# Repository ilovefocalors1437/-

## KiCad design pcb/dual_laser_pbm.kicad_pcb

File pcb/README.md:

# Dual-laser PBM head, REV 0.1 MOCK

This is a **mock reconstruction**. It stands in for the original design file, which is on another laptop. The schematic is not known, so this is a plausible, electrically sensible board built from scratch. It is not a copy of the original and may differ from it in every detail. The silkscreen says `REV 0.1 MOCK` on both sides.

It is a 2-layer KiCad 7 board for a photobiomodulation head with two laser diodes aimed at the foot fascia:

- **LD1, 660 nm (red):** the shallower channel. Design intent: help local blood flow.
- **LD2, 850 nm (near-IR):** the deeper channel, aimed at the fascia itself. Design intent: help loosen the hyaluronan (HA) layer in densified fascia.

Both are the user's design intent, not established clinical effects.

## Files

| Path | What |
|---|---|
| `dual_laser_pbm.kicad_pcb`, `.kicad_pro` | The board (KiCad 7.0). There is no schematic file; nets are assigned in the script. |
| `generate_board.py` | Builds the board with the pcbnew API: placement table, a small grid A* router with rip-up/retry, GND pours, stitching vias, silkscreen, DRC. |
| `drc_report.txt` | KiCad DRC output for the generated board. |
| `fab/` | Gerbers (F/B Cu, mask, silk, paste, Edge.Cuts), Excellon drill + drill map, pick-and-place CSV. |
| `renders/board-top.png`, `board-bottom.png` (+ `.svg`) | 2D renders from the real geometry (bottom is mirrored, as seen from below). |
| `renders/kicad-top.*`, `kicad-bottom.svg` | Raw `kicad-cli` SVG plots for reference. kicad-cli 7 draws bottom silk under the pour, so use `board-bottom.png` or the Gerber for bottom silk. |
| `export_viewer_data.py` → `viewer/board.json` | Board geometry for the 3D viewer: outline, drills, tracks, vias, pads, filled zones, silk, footprints. |
| `viewer/dual-laser-3d.html` | Interactive three.js viewer. Loads `board.json` from the same folder. |
| `renders/viewer-*.png` | Viewer screenshots (desktop and phone, light and dark, lasers on, bottom, net highlight, exploded). |

## Regenerate

Needs Ubuntu 24.04 with `kicad` 7.0.x, `kicad-footprints` and `librsvg2-bin`, and the system Python (`/usr/bin/python3`, which has `pcbnew`).

```sh
./build.sh     # board + DRC, fab outputs, viewer/board.json, 2D renders
```

The router is deterministic (the script pins `PYTHONHASHSEED`), so a rebuild gives the same geometry. Item UUIDs in the `.kicad_pcb` differ between runs. For the DRC footprint-vs-library check, KiCad needs a global `fp-lib-table` (copy `/usr/share/kicad/template/fp-lib-table` to `~/.config/kicad/7.0/`).

## Blocks

- **Power in:** J1 USB-C 6-pin power-only receptacle, R1/R2 5.1 k CC pull-downs, F1 500 mA PTC, D1 SMF5.0A TVS, C1 22 µF → +5V. U1 AP2112K-3.3 LDO (C2/C3) → +3V3 for the MCU.
- **MCU:** U2 STM32G030F6P6 (TSSOP-20), C4/C5 decoupling, C6 on NRST. J3 1×5 2.54 mm SWD header (3V3, SWCLK, GND, SWDIO, NRST). SW1 button on PA0. Status LEDs: D2 power (on +3V3), D3 660 active (PA2), D4 850 active (PA3).
- **Laser rail switch and interlock:** Q1 AO3401A P-FET switches +5V → VLD. R6 holds it off. Q2 2N7002 pulls Q1's gate down, but Q2's source only reaches GND through the J2 interlock loop, so VLD needs **MCU LASER_EN (PA12) AND a closed loop**. R7 keeps LASER_EN low during reset. The MCU reads the loop on PA11 (internal pull-up). D5 amber LED + R9 hang off VLD itself, so it is lit whenever the laser supply is live, whatever the firmware does. C7 10 µF on VLD.
- **Two constant-current channels** (ch1 = LD1, ch2 = LD2), one half of U3 MCP6002 each:
  MCU PWM (PA7 / PA6, TIM3) → 10 k / 1 k divider + 1 µF filter (R14/R15/C12, R19/R20/C14) → 0–0.30 V setpoint at IN+ → op-amp → 100 Ω gate resistor (R12/R17) → AO3400A sink (Q3/Q4) → 2.2 Ω 1206 sense (R11/R16) fed back to IN− through 1 k (R13/R18), 1 nF compensation from OUT to IN− (C11/C13). Full scale 0.30 V / 2.2 Ω = 136 mA. TP3/TP4 expose the sense voltages.
- **Laser protection:** each diode has a reverse Schottky (D6/D7, BAT60A) and 100 nF (C9/C10) across it.
- **Temperature:** TH1 10 k NTC (0603) between the cans, R10 10 k to +3V3, read on PA5 (ADC).
- **Lasers:** LD1/LD2 TO-56 (5.6 mm) 3-pin cans, KiCad `OptoDevice:LaserDiode_TO56-3`, 14 mm apart on the right edge, with a via-free ring around each can for a lens holder and a ring of GND thermal vias outside it.

## Design choices that differ from the brief

- Board is **58 × 38 mm** (brief: ~56 × 36) to give the router room. 4 × M2.5 plated holes on GND, 3 fiducials, 4 test points.
- The lasers are **14 mm apart** (brief: ~12) so two lens holders and the NTC fit between them.
- **No hardware interlock pull-up resistor.** The MCU's internal pull-up on PA11 does that job. This leaves a gap at R8 in the reference numbering.
- **Monitor photodiode unused:** pin 3 of each TO-56 (PD anode, assumed common-anode pinout) is tied to pin 2, which shorts the PD. Pinouts vary between laser diode vendors. Check the real part.
- Design rules: netclass clearance 0.15 mm, tracks 0.25 mm signal / 0.3 mm +3V3 / 0.6 mm for VBUS, +5V, VLD, LD cathodes and sense nodes, vias 0.6/0.3 mm, copper-to-edge 0.3 mm. The router aims for 0.2 mm, and the board also passes DRC with the clearance raised to 0.2 mm.
- MCU pins: PA0 BTN, PA2 LED_660, PA3 LED_850, PA5 NTC, PA6 PWM_850, PA7 PWM_660, PA11 interlock sense, PA12 LASER_EN, PA13/PA14 SWD. Unused pins (1, 2, 3, 8, 11, 15, 20) have no net, nor does U1 pin 4 (NC).

## Bill of materials

| Ref | Value | Footprint (KiCad 7 library) | Purpose |
|---|---|---|---|
| J1 | USB-C 6P power only | USB_C_Receptacle_GCT_USB4125-xx-x_6P_TopMnt_Horizontal | 5 V input |
| R1, R2 | 5.1k | R_0603_1608Metric | CC pull-downs (USB-C sink) |
| F1 | PTC 500 mA | Fuse_1206_3216Metric | Resettable input fuse |
| D1 | SMF5.0A | D_SOD-123F | TVS on +5V |
| C1 | 22 µF 10 V | C_1206_3216Metric | +5V bulk |
| U1 | AP2112K-3.3 | SOT-23-5 | 3.3 V LDO |
| C2, C3 | 1 µF | C_0603_1608Metric | LDO in/out |
| U2 | STM32G030F6P6 | TSSOP-20_4.4x6.5mm_P0.65mm | MCU |
| C4 / C5 / C6 | 100 nF / 1 µF / 100 nF | C_0603_1608Metric | MCU decoupling, NRST filter |
| J3 | SWD 1×5 | PinHeader_1x05_P2.54mm_Vertical | Programming header |
| SW1 | TL3342 | SW_SPST_TL3342 | Start/stop button |
| D2 / D3 / D4 | green / red / orange | LED_0603_1608Metric | Power / 660 active / 850 active |
| R3, R4, R5 | 1k | R_0603_1608Metric | Status LED resistors |
| Q1 | AO3401A | SOT-23 | High-side laser rail switch |
| R6 | 100k | R_0603_1608Metric | Q1 gate pull-up (off by default) |
| Q2 | 2N7002 | SOT-23 | Enable, sourced through the interlock |
| R7 | 100k | R_0603_1608Metric | LASER_EN pull-down |
| J2 | JST PH 2-pin | JST_PH_B2B-PH-K_1x02_P2.00mm_Vertical | Interlock loop |
| D5 | amber | LED_0603_1608Metric | Emission indicator on VLD |
| R9 | 1k | R_0603_1608Metric | Emission LED resistor |
| C7 | 10 µF | C_0805_2012Metric | VLD reservoir |
| U3 | MCP6002 | SOIC-8_3.9x4.9mm_P1.27mm | Dual op-amp, one loop per channel |
| C8 | 100 nF | C_0603_1608Metric | Op-amp decoupling |
| LD1 | 660 nm laser diode | LaserDiode_TO56-3 | Red channel |
| LD2 | 850 nm laser diode | LaserDiode_TO56-3 | Near-IR channel |
| Q3, Q4 | AO3400A | SOT-23 | Current sinks |
| R11, R16 | 2.2 Ω 1 % | R_1206_3216Metric | Current sense |
| R12, R17 | 100 Ω | R_0603_1608Metric | Gate resistors |
| R13, R18 | 1k | R_0603_1608Metric | Feedback resistors |
| C11, C13 | 1 nF | C_0603_1608Metric | Loop compensation |
| R14, R19 | 10k | R_0603_1608Metric | PWM divider top |
| R15, R20 | 1k | R_0603_1608Metric | PWM divider bottom |
| C12, C14 | 1 µF | C_0603_1608Metric | PWM filter |
| D6, D7 | BAT60A | D_SOD-323 | Reverse Schottky across each diode |
| C9, C10 | 100 nF | C_0603_1608Metric | Cap across each diode |
| TH1 | NTC 10k | R_0603_1608Metric | Temperature between the cans |
| R10 | 10k | R_0603_1608Metric | NTC divider |
| TP1–TP4 | +5V, +3V3, ISENSE1, ISENSE2 | TestPoint_Pad_D1.0mm | Test points |
| FID1–FID3 | | Fiducial_1mm_Mask2mm | Assembly fiducials |
| H1–H4 | M2.5 | MountingHole_2.7mm_M2.5_Pad | Mounting holes (GND) |

55 placed parts plus 4 test points, 3 fiducials and 4 holes (66 footprints).

## Nets (35)

Power: `VBUS` (J1 → F1), `+5V` (11 pads), `+3V3` (9), `VLD` (switched laser rail, 11), `GND` (36 pads; both layers poured and stitched).
Per laser channel n = 1, 2: `PWM_660`/`PWM_850`, `SETn`, `FBn`, `OUTn`, `GATEn`, `ISENSEn`, `LDn_K`.
Control: `LASER_EN`, `VLD_G`, `INTLK_LO`, `NTC_ADC`, `BTN`, `NRST`, `SWDIO`, `SWCLK`, `CC1`, `CC2`, `LED_660`, `LED_850`, `LEDA_PWR`, `LEDA_660`, `LEDA_850`, `LEDA_EMIT`.

Board stats: 539 track segments, 112 vias (routing + GND fanout + stitching), GND zones on F.Cu and B.Cu.

## What was verified, and what was not

Verified:
- KiCad 7 DRC (`pcbnew.WriteDRCReport`, all checks, zones filled): **0 violations, 0 unconnected pads, 0 footprint errors.** Also 0 clearance violations with the netclass clearance raised to 0.2 mm.
- Every net is routed. The connectivity check reports 0 unconnected items.
- Renders checked by eye: parts sit on their pads, there are no overlapping courtyards, and no silk sits on pads.

Not verified:
- No schematic, ERC, SPICE simulation or prototype. Values are textbook choices, not tuned.
- Q3/Q4 dissipate about 0.35 W each at full current from 5 V. That should be within an AO3400A's rating with this copper, but it was not thermally analysed.
- Footprint pinouts are taken from the KiCad libraries. The TO-56 pin assignment (which pin is common, whether the PD is common-anode) depends on the real laser part.
- Routing is machine-made. It is DRC-clean, but some signal runs are longer or more diagonal than a human would draw them, and +5V crosses under U2.
- Firmware does not exist. The PWM, interlock and NTC behaviour described here is what the hardware allows.

## Laser safety

A ~100 mW-class laser diode is Class 3B: direct or mirror-reflected beams can injure the eye. 850 nm is invisible, so there is no blink reflex and no visible cue that it is on. That is why this board has a hardware interlock, a hardware emission LED and current limits. A real device also needs wavelength-rated eyewear for anyone nearby, and a regulatory review (IEC 60825-1, plus medical-device rules if it is used on people) before use.

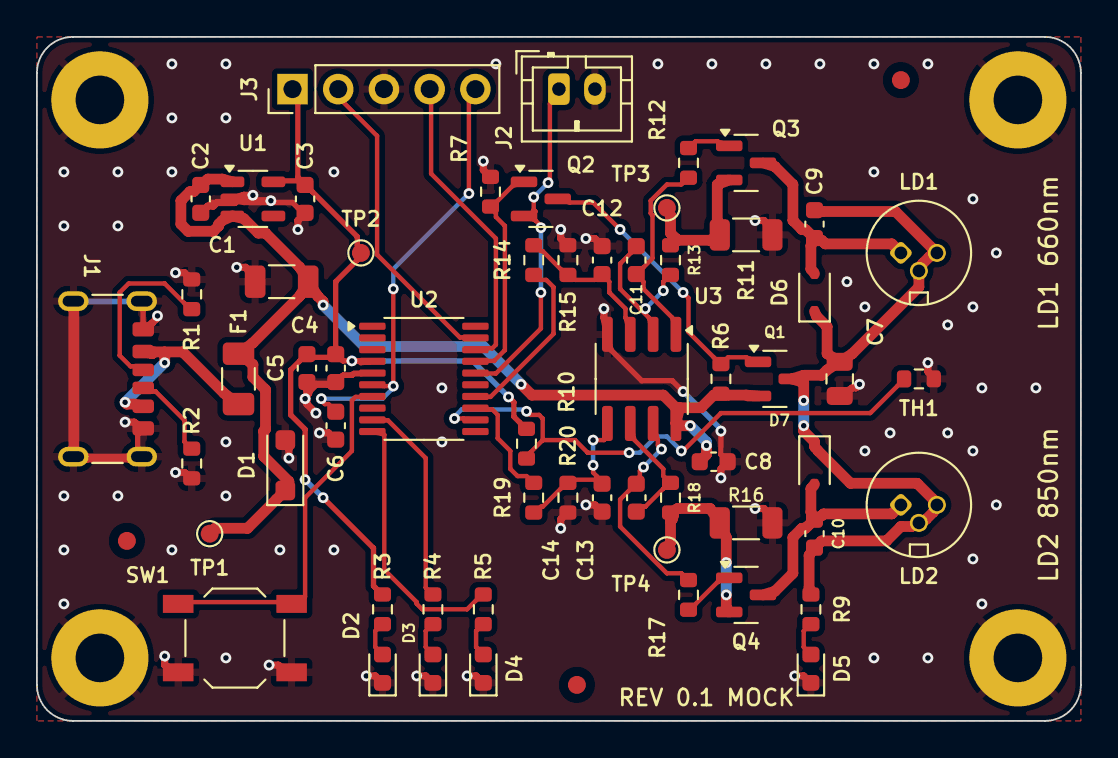
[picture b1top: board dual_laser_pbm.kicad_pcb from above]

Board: 2 copper layers, 58.0 x 38.0 mm, 66 parts (0 on the bottom side), 35 nets.

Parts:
C1: 22uF 10V; C_1206_3216Metric
C2, C3, C5, C12, C14: 1uF; C_0603_1608Metric
C4, C6, C8, C9, C10: 100nF; C_0603_1608Metric
C7: 10uF; C_0805_2012Metric
C11, C13: 1nF; C_0603_1608Metric
D1: SMF5.0A; D_SOD-123F
D2: green; LED_0603_1608Metric
D3: red; LED_0603_1608Metric
D4: orange; LED_0603_1608Metric
D5: amber; LED_0603_1608Metric
D6, D7: BAT60A; D_SOD-323
F1: PTC 500mA; Fuse_1206_3216Metric
FID1, FID2, FID3: FID; Fiducial_1mm_Mask2mm
H1, H2, H3, H4: M2.5; MountingHole_2.7mm_M2.5_Pad
J1: USB-C 6P (power only); USB_C_Receptacle_GCT_USB4125-xx-x_6P_TopMnt_Horizontal
J2: INTERLOCK; JST_PH_B2B-PH-K_1x02_P2.00mm_Vertical
J3: SWD 1x5; PinHeader_1x05_P2.54mm_Vertical
LD1: 660 nm LD; LaserDiode_TO56-3
LD2: 850 nm LD; LaserDiode_TO56-3
Q1: AO3401A; SOT-23
Q2: 2N7002; SOT-23
Q3, Q4: AO3400A; SOT-23
R1, R2: 5.1k; R_0603_1608Metric
R3, R4, R5, R9, R13, R15, R18, R20: 1k; R_0603_1608Metric
R6, R7: 100k; R_0603_1608Metric
R10, R14, R19: 10k; R_0603_1608Metric
R11, R16: 2.2R 1%; R_1206_3216Metric
R12, R17: 100R; R_0603_1608Metric
SW1: TL3342; SW_SPST_TL3342
TH1: NTC 10k; R_0603_1608Metric
TP1: +5V; TestPoint_Pad_D1.0mm
TP2: +3V3; TestPoint_Pad_D1.0mm
TP3: ISENSE1; TestPoint_Pad_D1.0mm
TP4: ISENSE2; TestPoint_Pad_D1.0mm
U1: AP2112K-3.3; SOT-23-5
U2: STM32G030F6P6; TSSOP-20_4.4x6.5mm_P0.65mm
U3: MCP6002; SOIC-8_3.9x4.9mm_P1.27mm

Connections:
+3V3: C3.2, C4.2, C5.2, J3.1, R3.2, R10.2, TP2.1, U1.5, U2.4
+5V: C1.2, C2.2, C8.1, D1.1, F1.2, Q1.2, R6.2, TP1.1, U1.1, U1.3, U3.8
BTN: SW1.1, U2.7
CC1: J1.A5, R1.1
CC2: J1.B5, R2.2
FB1: C11.2, R13.1, U3.2
FB2: C13.2, R18.1, U3.6
GATE1: Q3.1, R12.2
GATE2: Q4.1, R17.2
GND: C1.1, C2.1, C3.1, C4.1, C5.1, C6.1, C7.1, C8.2, C12.2, C14.2, D1.2, D2.1, D3.1, D4.1, D5.1, H1.1, H2.1, H3.1, H4.1, J1.A12, J1.B12, J1.S1, J2.2, J3.3, R1.2, R2.1, R7.1, R11.2, R15.2, R16.2, R20.2, SW1.2, TH1.2, U1.2, U2.5, U3.4
INTLK_LO: J2.1, Q2.2, U2.16
ISENSE1: Q3.2, R11.1, R13.2, TP3.1
ISENSE2: Q4.2, R16.1, R18.2, TP4.1
LASER_EN: Q2.1, R7.2, U2.17
LD1_K: C9.1, D6.2, LD1.1, Q3.3
LD2_K: C10.1, D7.2, LD2.1, Q4.3
LEDA_660: D3.2, R4.1
LEDA_850: D4.2, R5.1
LEDA_EMIT: D5.2, R9.1
LEDA_PWR: D2.2, R3.1
LED_660: R4.2, U2.9
LED_850: R5.2, U2.10
NRST: C6.2, J3.5, U2.6
NTC_ADC: R10.1, TH1.1, U2.12
OUT1: C11.1, R12.1, U3.1
OUT2: C13.1, R17.1, U3.7
PWM_660: R14.1, U2.14
PWM_850: R19.1, U2.13
SET1: C12.1, R14.2, R15.1, U3.3
SET2: C14.1, R19.2, R20.1, U3.5
SWCLK: J3.2, U2.19
SWDIO: J3.4, U2.18
VBUS: F1.1, J1.A9, J1.B9
VLD: C7.2, C9.2, C10.2, D6.1, D7.1, LD1.2, LD1.3, LD2.2, LD2.3, Q1.3, R9.2
VLD_G: Q1.1, Q2.3, R6.1
